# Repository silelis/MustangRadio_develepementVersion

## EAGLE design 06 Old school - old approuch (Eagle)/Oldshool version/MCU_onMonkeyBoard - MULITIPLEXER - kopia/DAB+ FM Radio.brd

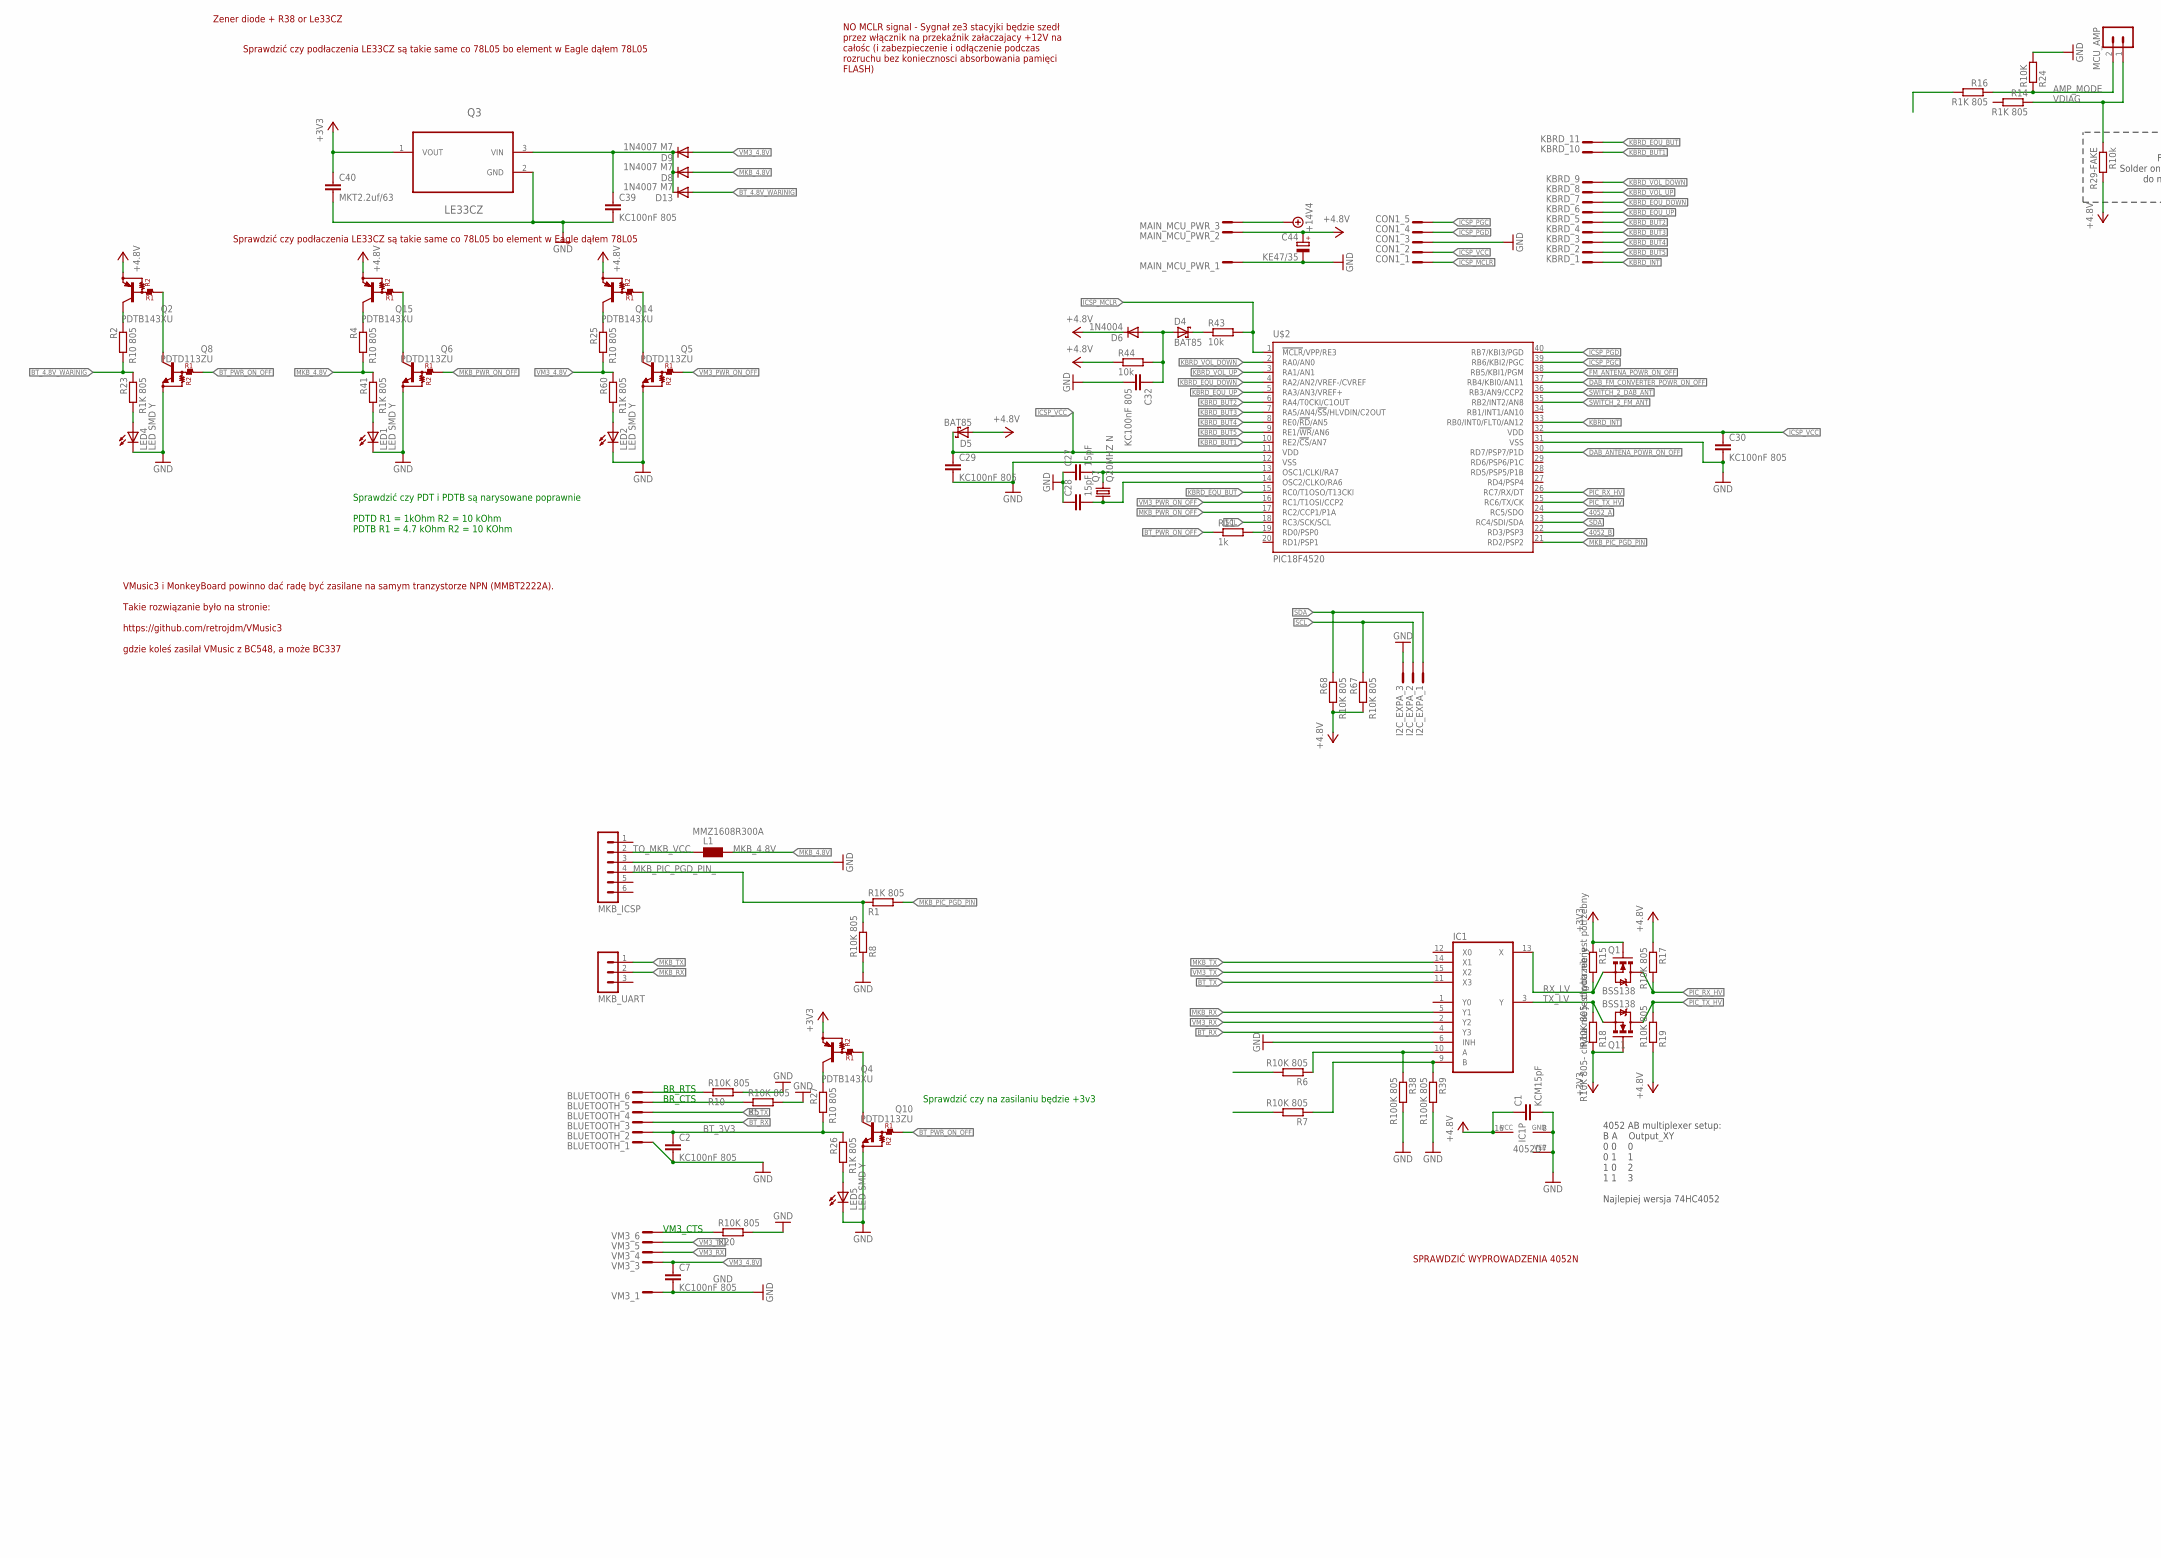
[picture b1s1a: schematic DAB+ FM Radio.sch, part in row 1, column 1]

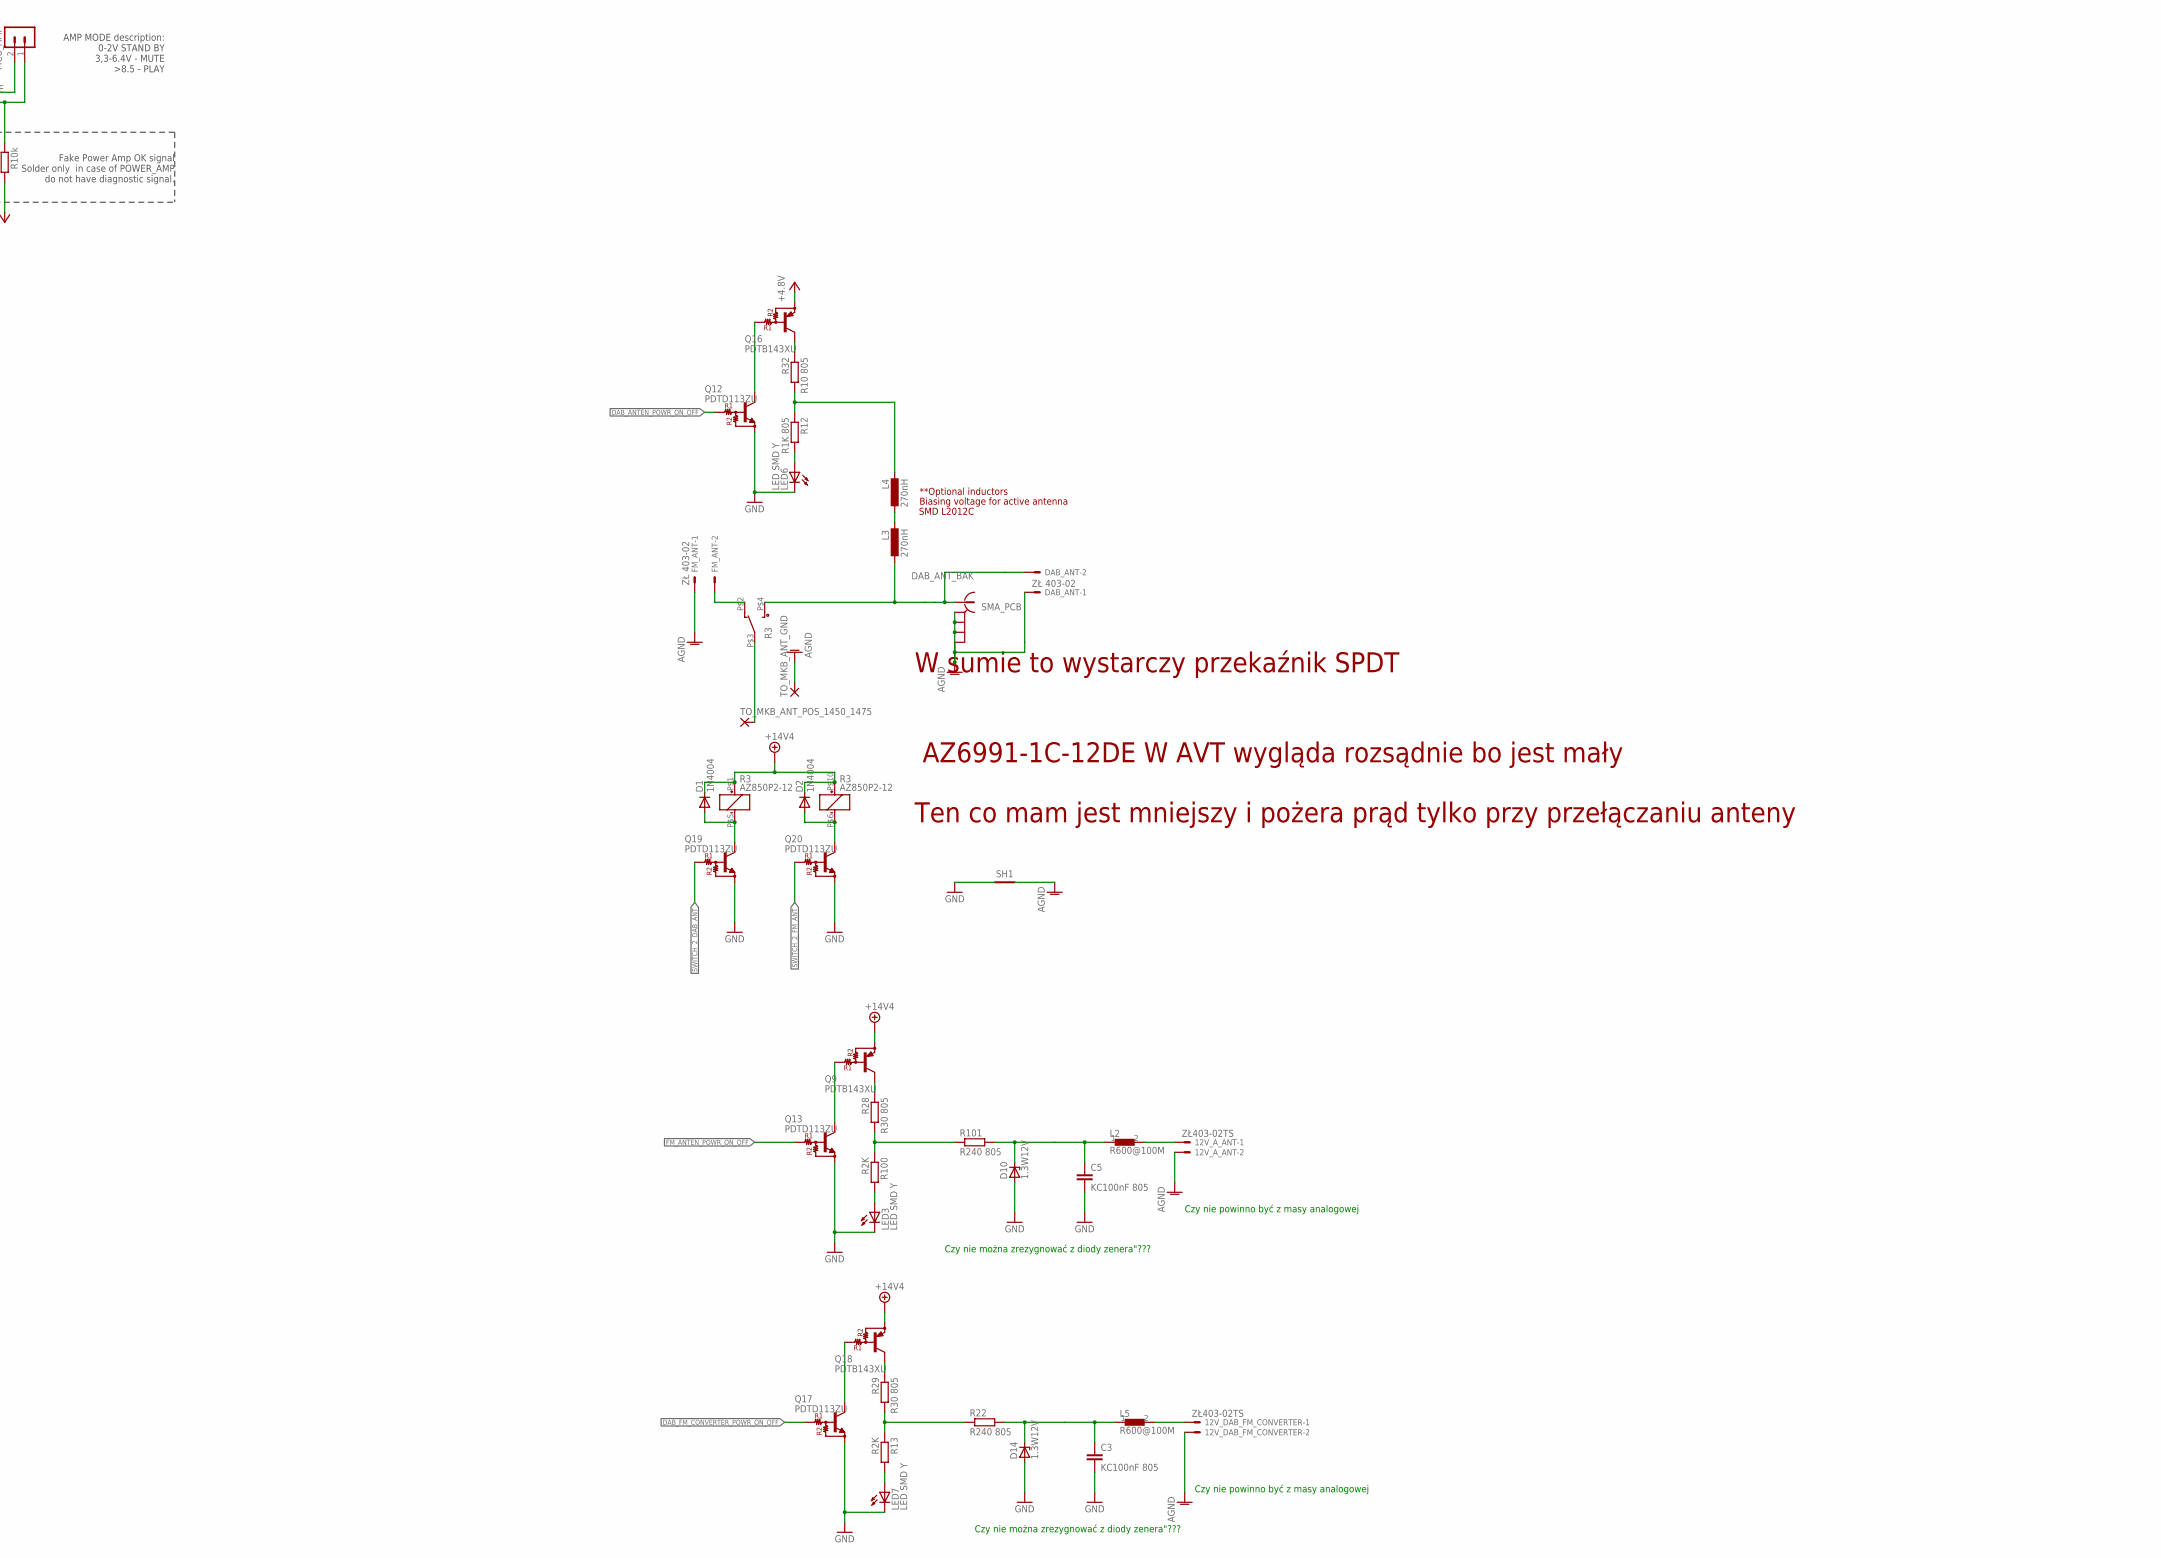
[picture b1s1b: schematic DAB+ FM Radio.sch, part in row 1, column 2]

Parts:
12V_A_ANT, 12V_DAB_FM_CONVERTER: ZŁ403-02TS; 22-23-2021
BLUETOOTH: JST_6_PIN_B6B-PH-KS; B6B-PH-KS
C1: KCM15pF; C0805
C2, C3, C5, C7, C29, C30, C32, C39: KC100nF 805; C0805
C27, C28: 15pF; C0805
C40: MKT2.2uf/63; C025-030X050
C44: KE47/35; TT2D6
CON1: JST_5_PIN_B5B-PH-KS; B5B-PH-KS
D1, D2: 1N4004; DO41-7.6
D4: BAT85; DO34-V
D5: BAT85; DO34-5
D6: 1N4004; DO41-V
D8, D9, D13: 1N4007 M7; DO41-V
D10, D14: 1.3W12V; ZDIO-2.5
DAB_ANT: ZŁ 403-02; 6410-02
DAB_ANT_BAK: SMA_PCB
FM_ANT: ZŁ 403-02; 6410-02
I2C_EXPA: JST_3_PIN_B3B-PH-KS; B3B-PH-KS
IC1: 4052D; SO16
KBRD: JST_11_PIN_B11B-PH-KS; B11B-PH-KS
L1: MMZ1608R300A; 0603
L2, L5: R600@100M; R0805
L3, L4: 270nH; L2012C
LED1, LED2, LED4, LED5: LED SMD Y; CHIP-LED0805
LED3, LED6, LED7: LED SMD Y; SMARTLED-TTW
MAIN_MCU_PWR: JST_3_PIN_B3B-XH-A; B3B-XH-A
MCU_AMP: MA02-1
MKB_ICSP: MA06-1
MKB_UART: MA03-1
Q1, Q11: BSS138; SOT23-3
Q2, Q4, Q9, Q14, Q15, Q16, Q18: PDTB143XU; SOT-23
Q3: LE33CZ; TO127P254X749-3
Q5, Q6, Q8, Q10, Q12, Q13, Q17, Q19, Q20: PDTD113ZU; SOT-23
Q7: Q20MHZ N; HC49/S
R1, R12, R14, R16, R23, R26, R41, R60: R1K 805; R0805
R2, R4, R25, R27, R32: R10 805; R0805
R3: AZ850P2-12; AZ850-2C
R5, R6, R7, R8, R10, R17, R19, R20, R67, R68: R10K 805; R0805
R11: 1k; R0805
R13, R100: R2K; R0805
R15, R18: R10K 805- chyba nie jest potrzebny; R0805
R22, R101: R240 805; M0805
R24: R10K; R0805
R28, R29: R30 805; R0805
R29-FAKE: R10k; 0204/7
R38, R39: R100K 805; M0805
R43: 10k; R0805
R44: 10k; M0805
SH1: SHORT-HT5; SHORT_TOP-50
TO_MKB_ANT_GND: 2,54/0,8
TO_MKB_ANT_POS_1450_1475: 2,54/0,8
U$2: PIC18F4520; DIL40
VM3: JST_6_PIN_B6B-PH-KS; B6B-PH-KS

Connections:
4052_A: R6.2, U$2.24 (RC5/SDO)
4052_B: R7.2, U$2.22 (RD3/PSP3)
+3V3: C40.1, Q1.1 (G), Q3.1 (VOUT), Q4.2 (E), Q11.1 (G), R15.1, R18.1
+5V: C1.1, C44.+, D5.A, D6.C, IC1.16 (VCC), MAIN_MCU_PWR.P$2, Q2.2 (E), Q14.2 (E), Q15.2 (E), Q16.2 (E), R17.1, R19.1, R29-FAKE.2, R44.1, R67.2, R68.2
+14V4: D1.C, D2.C, MAIN_MCU_PWR.P$3, Q9.2 (E), Q18.2 (E), R3.P$1 (+), R3.P$10 (+)
AGND: 12V_A_ANT.2, 12V_DAB_FM_CONVERTER.2, DAB_ANT.1, DAB_ANT_BAK.GND@1 (GND), DAB_ANT_BAK.GND@2 (GND), DAB_ANT_BAK.GND@3 (GND), DAB_ANT_BAK.GND@4 (GND), FM_ANT.1, SH1.2, TO_MKB_ANT_GND.1
AMP_MODE: MCU_AMP.2, R16.1, R24.1
BT_3V3: BLUETOOTH.P$2, C2.1, R26.1, R27.2
BT_4.8V_WARINIG: D13.A, R2.2, R23.1
BT_PWR_ON_OFF: Q8.1 (B), Q10.1 (B), R11.1
BT_RX: BLUETOOTH.P$3, IC1.4 (Y3)
BT_TX: BLUETOOTH.P$4, IC1.11 (X3)
DAB_ANTENA_POWR_ON_OFF: U$2.30 (RD7/PSP7/P1D)
DAB_ANTEN_POWR_ON_OFF: Q12.1 (B)
DAB_FM_CONVERTER_POWR_ON_OFF: Q17.1 (B), U$2.37 (RB4/KBI0/AN11)
FM_ANTENA_POWR_ON_OFF: U$2.38 (RB5/KBI1/PGM)
FM_ANTEN_POWR_ON_OFF: Q13.1 (B)
GND: BLUETOOTH.P$1, C1.2, C2.2, C3.2, C5.2, C7.2, C27.1, C28.1, C29.2, C30.2, C32.2, C39.2, C40.2, C44.-, CON1.P$3, D10.A, D14.A, I2C_EXPA.P$3, IC1.6 (INH), IC1.7 (VEE), IC1.8 (GND), LED1.C, LED2.C, LED3.C@1 (C), LED4.C, LED5.C, LED6.C@1 (C), LED7.C@1 (C), MAIN_MCU_PWR.P$1, MKB_ICSP.3, Q3.2 (GND), Q5.2 (E), Q6.2 (E), Q8.2 (E), Q10.2 (E), Q12.2 (E), Q13.2 (E), Q17.2 (E), Q19.2 (E), Q20.2 (E), R5.2, R8.1, R10.2, R20.2, R24.2, R38.2, R39.2, SH1.1, U$2.12 (VSS), U$2.31 (VSS), VM3.P$1
ICSP_MCLR: CON1.P$1, R43.2, U$2.1 (!MCLR!/VPP/RE3)
ICSP_PGC: CON1.P$5, U$2.39 (RB6/KBI2/PGC)
ICSP_PGD: CON1.P$4, U$2.40 (RB7/KBI3/PGD)
ICSP_VCC: C29.1, C30.1, CON1.P$2, D5.C, U$2.11 (VDD), U$2.32 (VDD)
KBRD_BUT1: KBRD.P$10, U$2.10 (RE2/!CS!/AN7)
KBRD_BUT2: KBRD.P$5, U$2.6 (RA4/T0CKI/C1OUT)
KBRD_BUT3: KBRD.P$4, U$2.7 (RA5/AN4/!SS!/HLVDIN/C2OUT)
KBRD_BUT4: KBRD.P$3, U$2.8 (RE0/!RD!/AN5)
KBRD_BUT5: KBRD.P$2, U$2.9 (RE1/!WR!/AN6)
KBRD_EQU_BUT: KBRD.P$11, U$2.15 (RC0/T1OSO/T13CKI)
KBRD_EQU_DOWN: KBRD.P$7, U$2.4 (RA2/AN2/VREF-/CVREF)
KBRD_EQU_UP: KBRD.P$6, U$2.5 (RA3/AN3/VREF+)
KBRD_INT: KBRD.P$1, U$2.33 (RB0/INT0/FLT0/AN12)
KBRD_VOL_DOWN: KBRD.P$9, U$2.2 (RA0/AN0)
KBRD_VOL_UP: KBRD.P$8, U$2.3 (RA1/AN1)
MKB_4.8V: D8.A, L1.2, R4.2, R41.1
MKB_PIC_PGD_PIN: R1.2, U$2.21 (RD2/PSP2)
MKB_PIC_PGD_PIN_: MKB_ICSP.4, R1.1, R8.2
MKB_PWR_ON_OFF: Q6.1 (B), U$2.17 (RC2/CCP1/P1A)
MKB_RX: IC1.5 (Y1), MKB_UART.2
MKB_TX: IC1.14 (X1), MKB_UART.1
unnamed: L4.1, R12.1, R32.2
unnamed: D1.A, Q19.3 (C), R3.P$5 (-)
unnamed: R3.P$3 (5), TO_MKB_ANT_POS_1450_1475.1
unnamed: DAB_ANT.2, DAB_ANT_BAK.P$1 (1), L3.2, R3.P$4 (6)
unnamed: FM_ANT.2, R3.P$2 (4)
unnamed: D2.A, Q20.3 (C), R3.P$6 (-)
unnamed: Q2.3 (C), R2.1
unnamed: L3.1, L4.2
unnamed: IC1.9 (B), R7.1, R39.1
unnamed: C27.2, Q7.2, U$2.13 (OSC1/CLKI/RA7)
unnamed: C28.2, Q7.1, U$2.14 (OSC2/CLKO/RA6)
unnamed: R11.2, U$2.19 (RD0/PSP0)
unnamed: Q15.3 (C), R4.1
unnamed: Q2.1 (B), Q8.3 (C)
unnamed: Q12.3 (C), Q16.1 (B)
unnamed: LED4.A, R23.2
unnamed: Q4.1 (B), Q10.3 (C)
unnamed: LED6.A@1 (A), R12.2
unnamed: LED5.A, R26.2
unnamed: Q17.3 (C), Q18.1 (B)
unnamed: R13.1, R22.1, R29.2
unnamed: LED7.A@1 (A), R13.2
unnamed: Q5.3 (C), Q14.1 (B)
unnamed: C3.1, D14.C, L5.1, R22.2
unnamed: 12V_DAB_FM_CONVERTER.1, L5.2
unnamed: LED2.A, R60.2
unnamed: Q14.3 (C), R25.1
unnamed: Q16.3 (C), R32.1
unnamed: Q9.3 (C), R28.1
unnamed: Q18.3 (C), R29.1
unnamed: Q4.3 (C), R27.1
unnamed: Q6.3 (C), Q15.1 (B)
unnamed: BLUETOOTH.P$5, R5.1
unnamed: LED1.A, R41.2
unnamed: D4.C, R43.1
unnamed: C32.1, D4.A, D6.A, R44.2
unnamed: BLUETOOTH.P$6, R10.1
unnamed: R20.1, VM3.P$6
unnamed: IC1.10 (A), R6.1, R38.1
unnamed: C39.1, D8.C, D9.C, D13.C, Q3.3 (VIN)
unnamed: Q9.1 (B), Q13.3 (C)
unnamed: R28.2, R100.1, R101.1
unnamed: LED3.A@1 (A), R100.2
unnamed: C5.1, D10.C, L2.1, R101.2
unnamed: 12V_A_ANT.1, L2.2
PIC_RX_HV: Q1.3 (D), R17.2, U$2.26 (RC7/RX/DT)
PIC_TX_HV: Q11.3 (D), R19.2, U$2.25 (RC6/TX/CK)
RX_LV: IC1.13 (X), Q1.2 (S), R15.2
SCL: I2C_EXPA.P$2, R67.1, U$2.18 (RC3/SCK/SCL)
SDA: I2C_EXPA.P$1, R68.1, U$2.23 (RC4/SDI/SDA)
SWITCH_2_DAB_ANT: Q19.1 (B), U$2.36 (RB3/AN9/CCP2)
SWITCH_2_FM_ANT: Q20.1 (B), U$2.35 (RB2/INT2/AN8)
TO_MKB_VCC: L1.1, MKB_ICSP.2
TX_LV: IC1.3 (Y), Q11.2 (S), R18.2
VDIAG: MCU_AMP.1, R14.1, R29-FAKE.1
VM3_4.8V: C7.1, D9.A, R25.2, R60.1, VM3.P$3
VM3_PWR_ON_OFF: Q5.1 (B), U$2.16 (RC1/T1OSI/CCP2)
VM3_RX: IC1.2 (Y2), VM3.P$4
VM3_TX: IC1.15 (X2), VM3.P$5

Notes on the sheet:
AMP MODE description: 0-2V STAND BY 3,3-6.4V - MUTE >8.5 - PLAY
Fake Power Amp OK signal Solder only in case of POWER_AMP do not have diagnostic signal.
NO MCLR signal - Sygnał ze3 stacyjki będzie szedł przez włącznik na przekaźnik załaczajacy +12V na całośc (i zabezpieczenie i odłączenie podczas rozruchu bez koniecznosci absorbowania pamięci FLASH)
Sprawdzić czy podłaczenia LE33CZ są takie same co 78L05 bo element w Eagle dąłem 78L05
Sprawdzić czy PDT i PDTB są narysowane poprawnie PDTD R1 = 1kOhm R2 = 10 kOhm PDTB R1 = 4.7 kOhm R2 = 10 KOhm
W sumie to wystarczy przekaźnik SPDT AZ6991-1C-12DE W AVT wygląda rozsądnie bo jest mały Ten co mam jest mniejszy i pożera prąd tylko przy przełączaniu anteny
**Optional inductors
Biasing voltage for active antenna
SMD L2012C
Czy nie powinno być z masy analogowej
VMusic3 i MonkeyBoard powinno dać radę być zasilane na samym tranzystorze NPN (MMBT2222A). Takie rozwiązanie było na stronie: https://github.com/retrojdm/VMusic3 gdzie koleś zasilał VMusic z BC548, a może BC337
SPRAWDZIĆ WYPROWADZENIA 4052N
4052 AB multiplexer setup: B A Output_XY 0 0 0 0 1 1 1 0 2 1 1 3 Najlepiej wersja 74HC4052
VM3_CTS
BR_CTS
BR_RTS
Sprawdzić czy na zasilaniu będzie +3v3
Czy nie można zrezygnować z diody zenera"???
Zener diode + R38 or Le33CZ

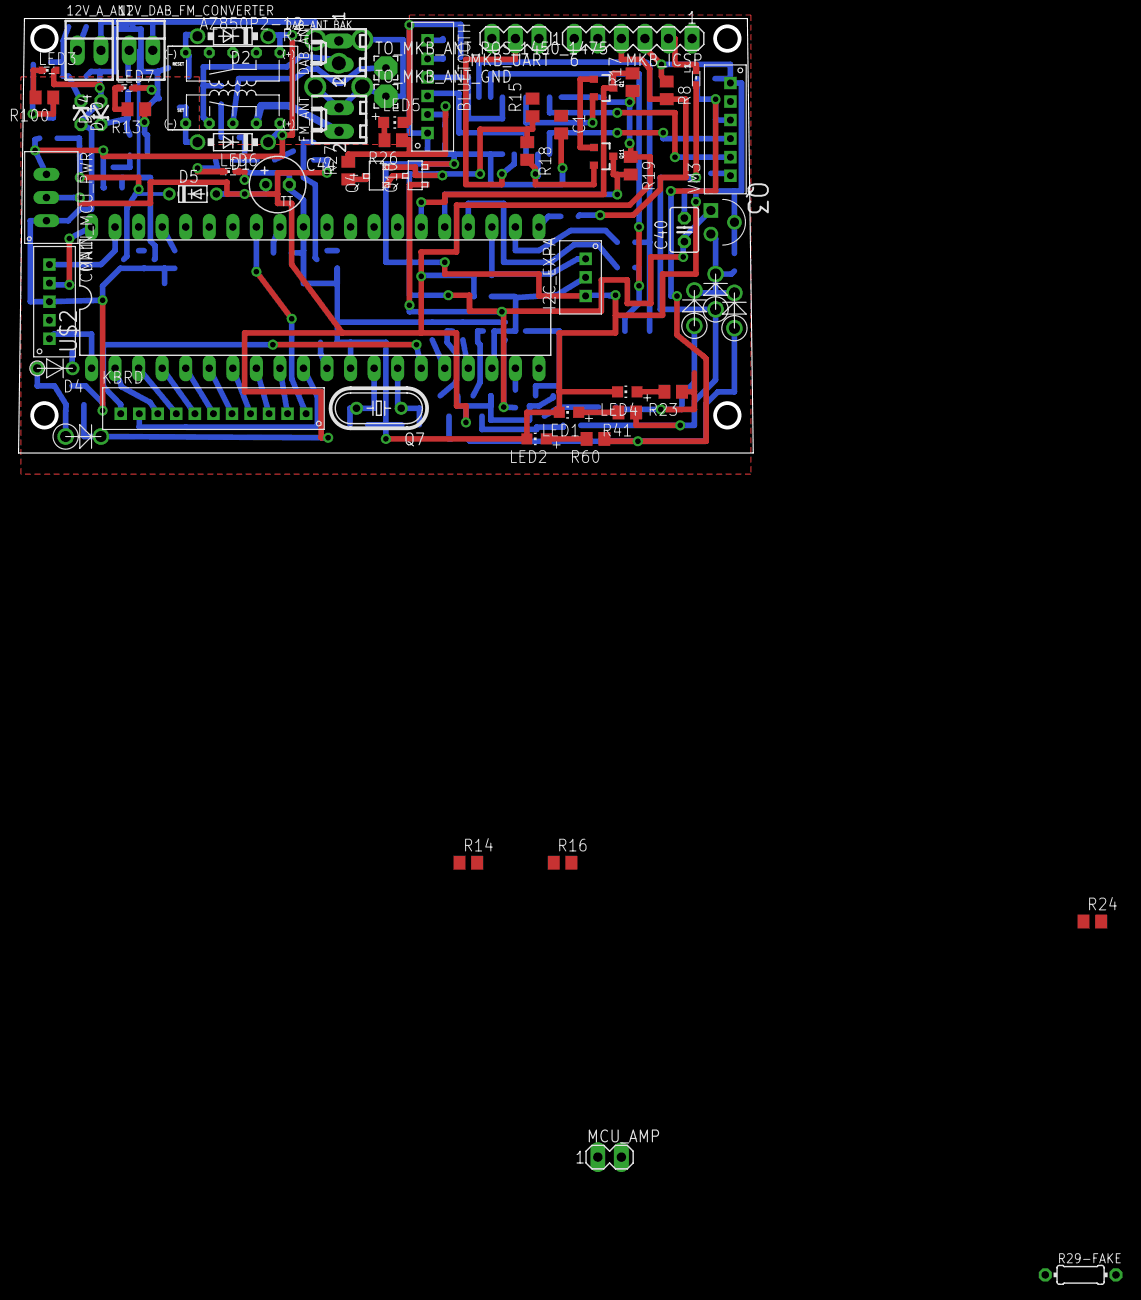
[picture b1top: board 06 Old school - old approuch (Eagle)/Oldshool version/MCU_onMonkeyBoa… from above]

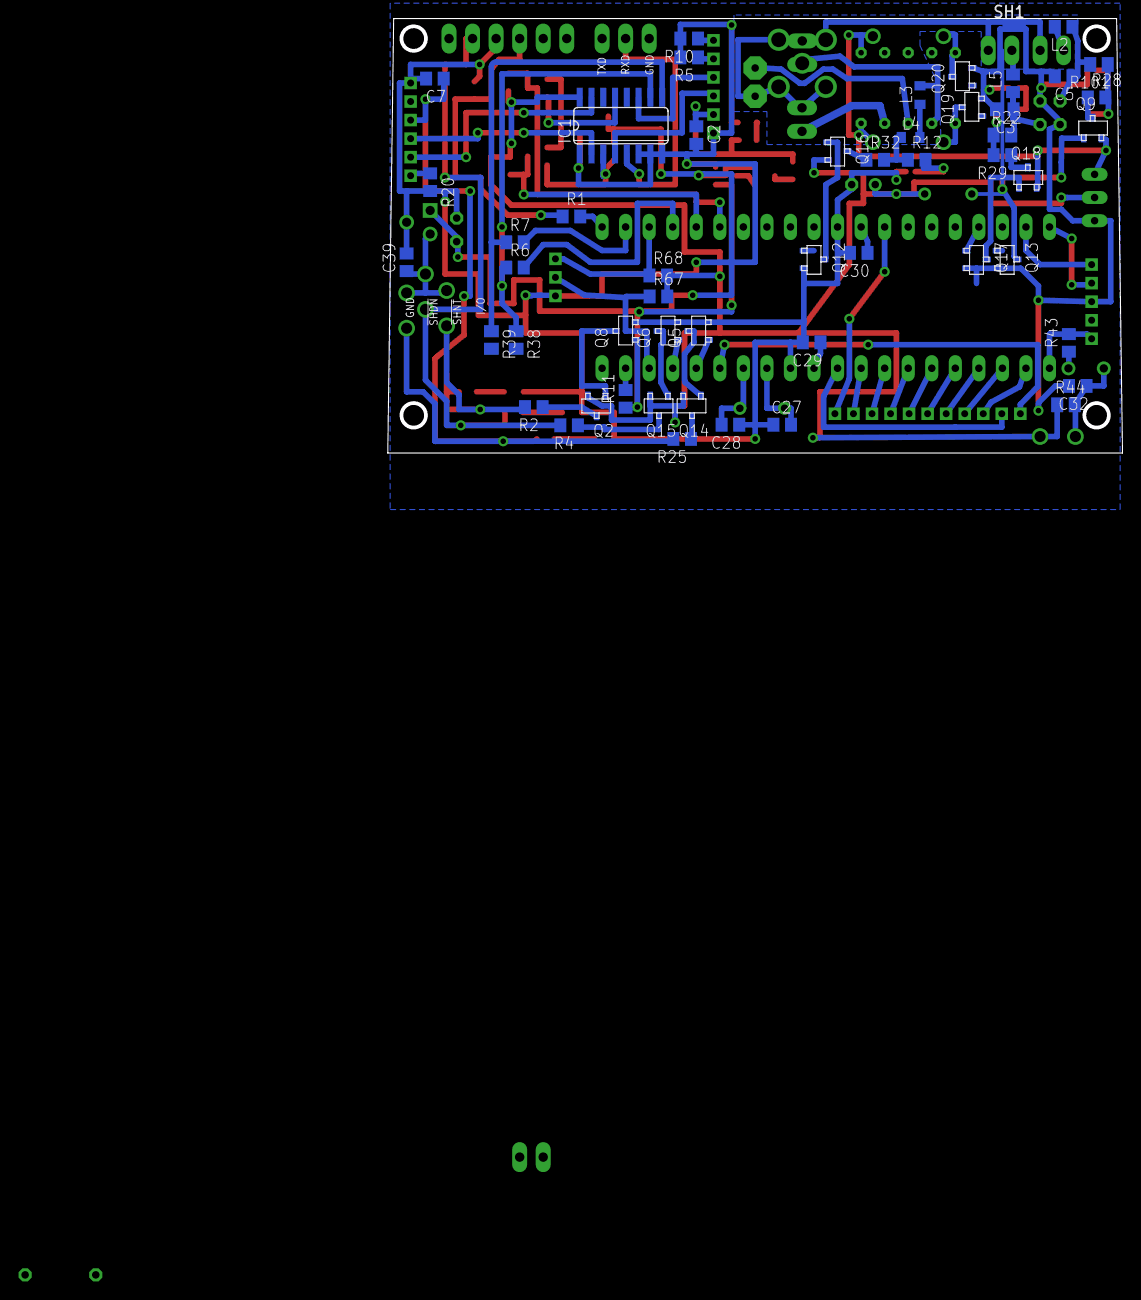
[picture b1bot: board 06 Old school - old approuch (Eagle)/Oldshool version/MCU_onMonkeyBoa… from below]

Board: 2 copper layers, 79.2 x 46.9 mm, 113 parts (52 on the bottom side), 94 nets.

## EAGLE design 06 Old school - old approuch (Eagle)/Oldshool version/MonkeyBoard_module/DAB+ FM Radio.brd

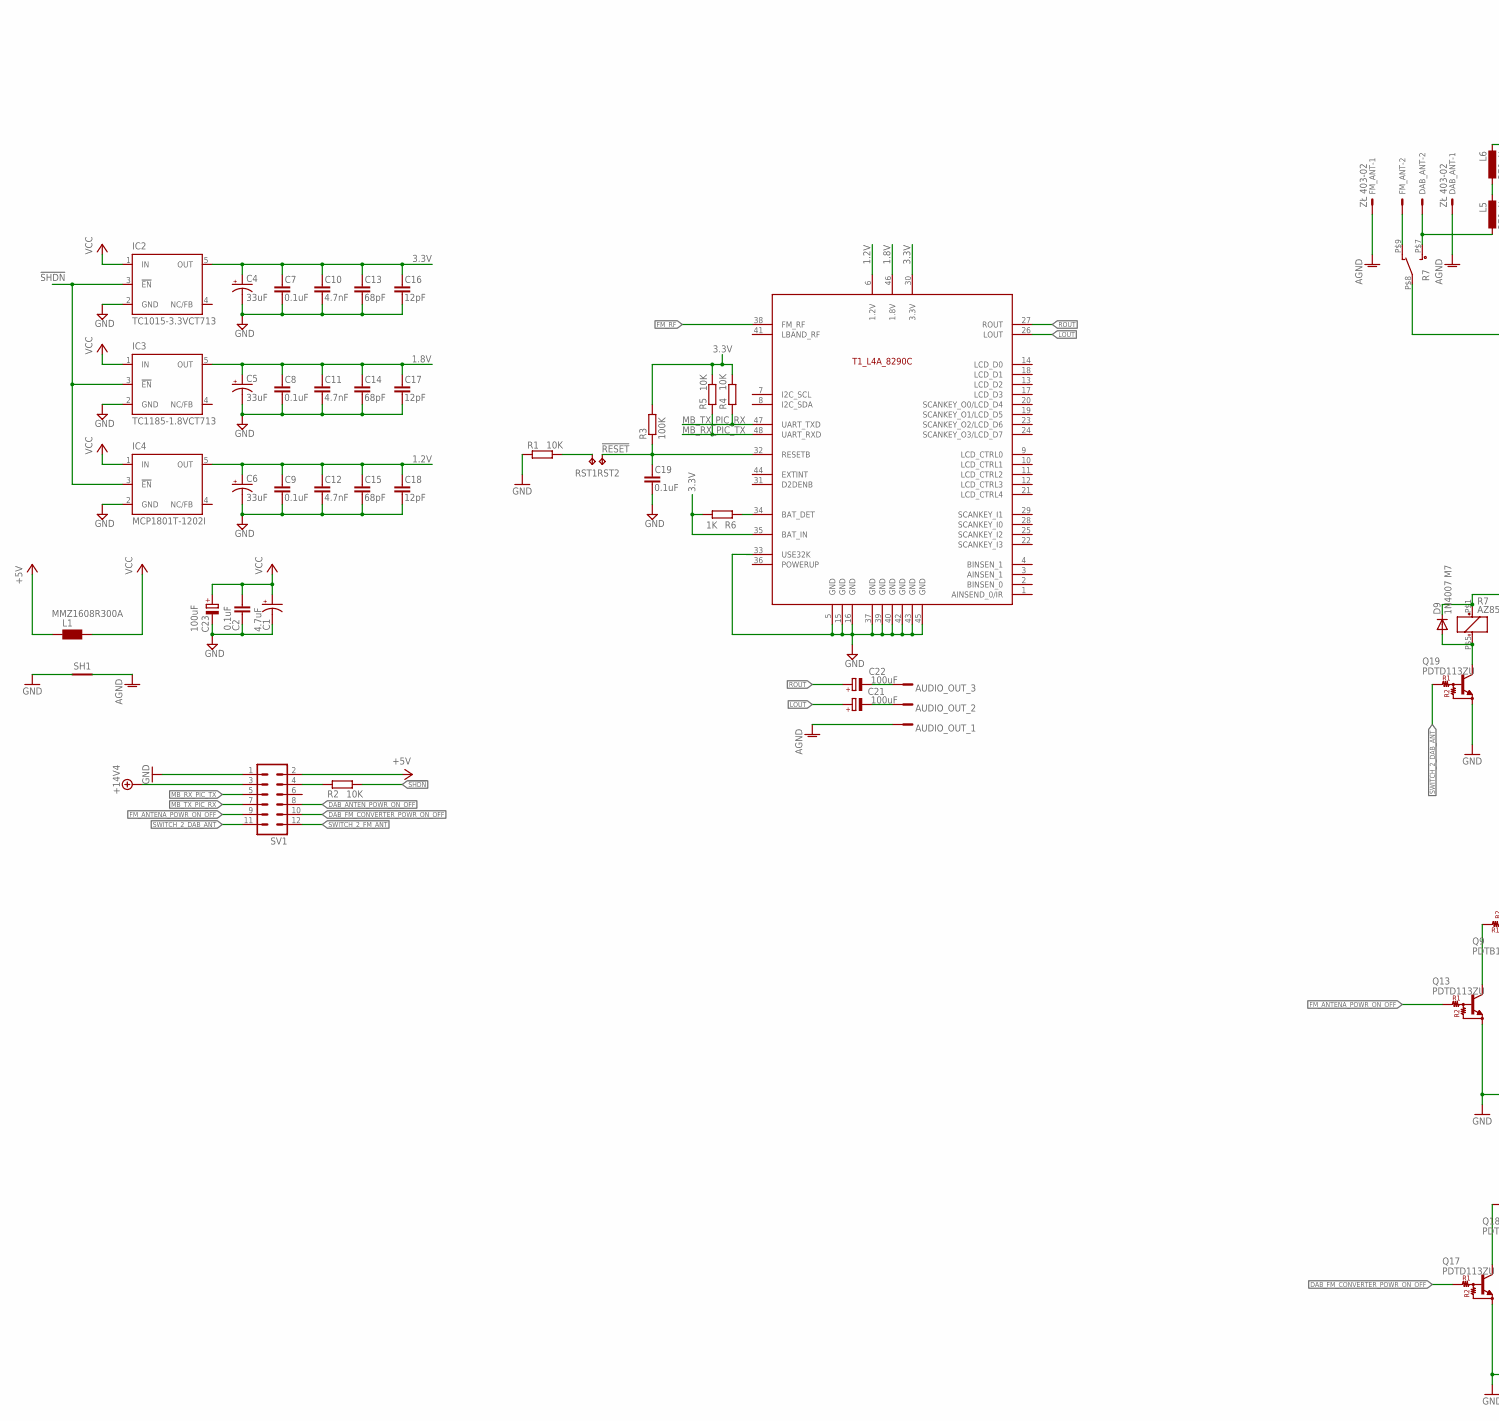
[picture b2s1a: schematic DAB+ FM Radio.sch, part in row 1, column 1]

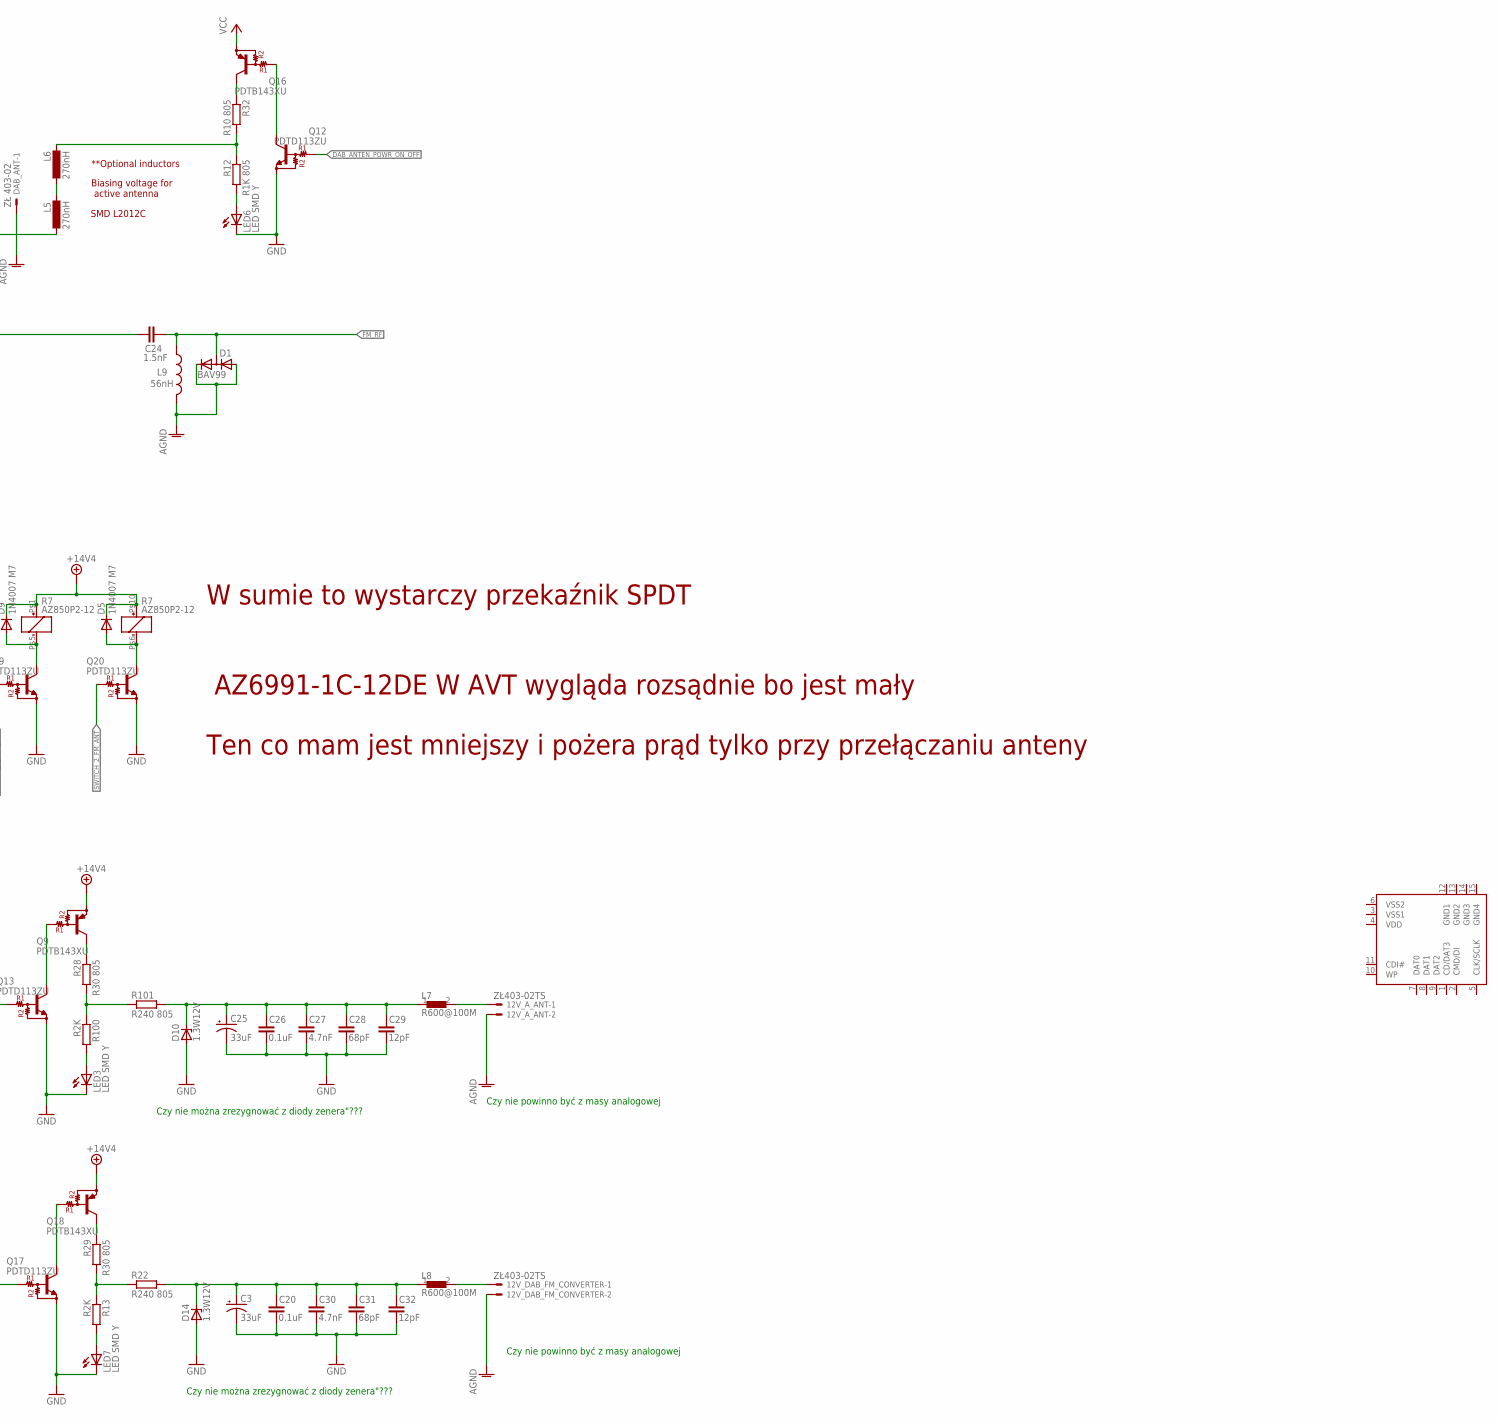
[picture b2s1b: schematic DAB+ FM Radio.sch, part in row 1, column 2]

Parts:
12V_A_ANT, 12V_DAB_FM_CONVERTER: ZŁ403-02TS; 22-23-2021
AUDIO_OUT: JST_3_PIN_B3B-PH-KS; B3B-PH-KS
C1: 4.7uF; EIA3216
C2, C7, C8, C9, C19, C20, C26: 0.1uF; C0603
C3, C4, C5, C6, C25: 33uF; EIA3216
C10, C11, C12, C27, C30: 4.7nF; C0603
C13, C14, C15, C28, C31: 68pF; C0603
C16, C17, C18, C29, C32: 12pF; C0603
C21, C22, C23: 100uF; PANASONIC_D
C24: 1.5nF; C0603
D1: BAV99; SOT23
D5, D9: 1N4007 M7; SOD-123_MINI-SMA
D10, D14: 1.3W12V; ZDIO-2.5
DAB_ANT: ZŁ 403-02; 6410-02
FM_ANT: ZŁ 403-02; 6410-02
IC2: TC1015-3.3VCT713; SOT23-DBV
IC3: TC1185-1.8VCT713; SOT23-DBV
IC4: MCP1801T-1202I; SOT23-DBV
L1: MMZ1608R300A; 0603
L5, L6: 270nH; L2012C
L7, L8: R600@100M; R0805
L9: 56nH; 0603
LED3, LED6, LED7: LED SMD Y; SMARTLED-TTW
Q9, Q16, Q18: PDTB143XU; SOT-23
Q12, Q13, Q17, Q19, Q20: PDTD113ZU; SOT-23
R1, R2, R4, R5: 10K; R0603
R3: 100K; R0603
R6: 1K; R0603
R7: AZ850P2-12; AZ850-2C
R12: R1K 805; R0805
R13, R100: R2K; R0805
R22, R101: R240 805; M0805
R28, R29: R30 805; R0805
R32: R10 805; R0805
RST1, RST2: TPB1,27; B1,27
SH1: SHORT-HT5; SHORT_TOP-50
SV1: MA06-2
U$1: T1_L4A_8290C/T2_L4A_8650C; T1_L4A
U$6: ZŁ KART SD; SDCMF-10915W010

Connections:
1.2V: C6.A (+), C9.1, C12.1, C15.1, C18.1, IC4.5 (OUT), U$1.6 (1.2V)
1.8V: C5.A (+), C8.1, C11.1, C14.1, C17.1, IC3.5 (OUT), U$1.46 (1.8V)
3.3V: C4.A (+), C7.1, C10.1, C13.1, C16.1, IC2.5 (OUT), R3.2, R4.2, R5.2, R6.2, U$1.30 (3.3V), U$1.35 (BAT_IN)
!RESET!: C19.1, R3.1, RST2.TP, U$1.32 (RESETB)
!SHDN!: IC2.3 (!EN), IC3.3 (!EN), IC4.3 (!EN), R2.2
+5V: L1.1, SV1.2
+12V: D5.C, D9.C, Q9.2 (E), Q18.2 (E), R7.P$1 (+), R7.P$10 (+), SV1.3
AGND: 12V_A_ANT.2, 12V_DAB_FM_CONVERTER.2, AUDIO_OUT.P$1, D1.1 (A), D1.2 (C), DAB_ANT.1, FM_ANT.1, L9.2, SH1.2
DAB_ANTEN_POWR_ON_OFF: Q12.1 (B), SV1.8
DAB_FM_CONVERTER_POWR_ON_OFF: Q17.1 (B), SV1.10
FM_ANTENA_POWR_ON_OFF: Q13.1 (B), SV1.9
FM_RF: C24.2, D1.3 (AC), L9.1, U$1.38 (FM_RF)
GND: C1.C (-), C2.2, C3.C (-), C4.C (-), C5.C (-), C6.C (-), C7.2, C8.2, C9.2, C10.2, C11.2, C12.2, C13.2, C14.2, C15.2, C16.2, C17.2, C18.2, C19.2, C20.2, C23.-, C25.C (-), C26.2, C27.2, C28.2, C29.2, C30.2, C31.2, C32.2, D10.A, D14.A, IC2.2 (GND), IC3.2 (GND), IC4.2 (GND), LED3.C@1 (C), LED6.C@1 (C), LED7.C@1 (C), Q12.2 (E), Q13.2 (E), Q17.2 (E), Q19.2 (E), Q20.2 (E), R1.1, SH1.1, SV1.1, U$1.5 (GND), U$1.15 (GND), U$1.16 (GND), U$1.33 (USE32K), U$1.37 (GND), U$1.39 (GND), U$1.40 (GND), U$1.42 (GND), U$1.43 (GND), U$1.45 (GND)
GND1: U$6.12 (GND1)
GND2: U$6.13 (GND2)
GND3: U$6.14 (GND3)
GND4: U$6.15 (GND4)
LOUT: C21.+, U$1.26 (LOUT)
MB_RX_PIC_TX: R5.1, SV1.5, U$1.48 (UART_RXD)
MB_TX_PIC_RX: R4.1, SV1.7, U$1.47 (UART_TXD)
unnamed: D5.A, Q20.3 (C), R7.P$6 (-)
unnamed: D9.A, Q19.3 (C), R7.P$5 (-)
unnamed: R6.1, U$1.34 (BAT_DET)
unnamed: C24.1, R7.P$8 (5)
unnamed: DAB_ANT.2, L5.2, R7.P$7 (6)
unnamed: AUDIO_OUT.P$3, C22.-
unnamed: FM_ANT.2, R7.P$9 (4)
unnamed: AUDIO_OUT.P$2, C21.-
unnamed: L6.1, R12.1, R32.2
unnamed: R2.1, SV1.4
unnamed: L5.1, L6.2
unnamed: R1.2, RST1.TP
unnamed: Q12.3 (C), Q16.1 (B)
unnamed: LED6.A@1 (A), R12.2
unnamed: Q17.3 (C), Q18.1 (B)
unnamed: R13.1, R22.1, R29.2
unnamed: LED7.A@1 (A), R13.2
unnamed: C3.A (+), C20.1, C30.1, C31.1, C32.1, D14.C, L8.1, R22.2
unnamed: 12V_DAB_FM_CONVERTER.1, L8.2
unnamed: Q16.3 (C), R32.1
unnamed: Q9.3 (C), R28.1
unnamed: Q18.3 (C), R29.1
unnamed: Q9.1 (B), Q13.3 (C)
unnamed: R28.2, R100.1, R101.1
unnamed: LED3.A@1 (A), R100.2
unnamed: C25.A (+), C26.1, C27.1, C28.1, C29.1, D10.C, L7.1, R101.2
unnamed: 12V_A_ANT.1, L7.2
ROUT: C22.+, U$1.27 (ROUT)
SWITCH_2_DAB_ANT: Q19.1 (B), SV1.11
SWITCH_2_FM_ANT: Q20.1 (B), SV1.12
VCC: C1.A (+), C2.1, C23.+, IC2.1 (IN), IC3.1 (IN), IC4.1 (IN), L1.2, Q16.2 (E)
VDD: U$6.4 (VDD)
VSS1: U$6.3 (VSS1)
VSS2: U$6.6 (VSS2)

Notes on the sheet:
W sumie to wystarczy przekaźnik SPDT AZ6991-1C-12DE W AVT wygląda rozsądnie bo jest mały Ten co mam jest mniejszy i pożera prąd tylko przy przełączaniu anteny
**Optional inductors
Biasing voltage for active antenna
SMD L2012C
Czy nie powinno być z masy analogowej
Czy nie można zrezygnować z diody zenera"???

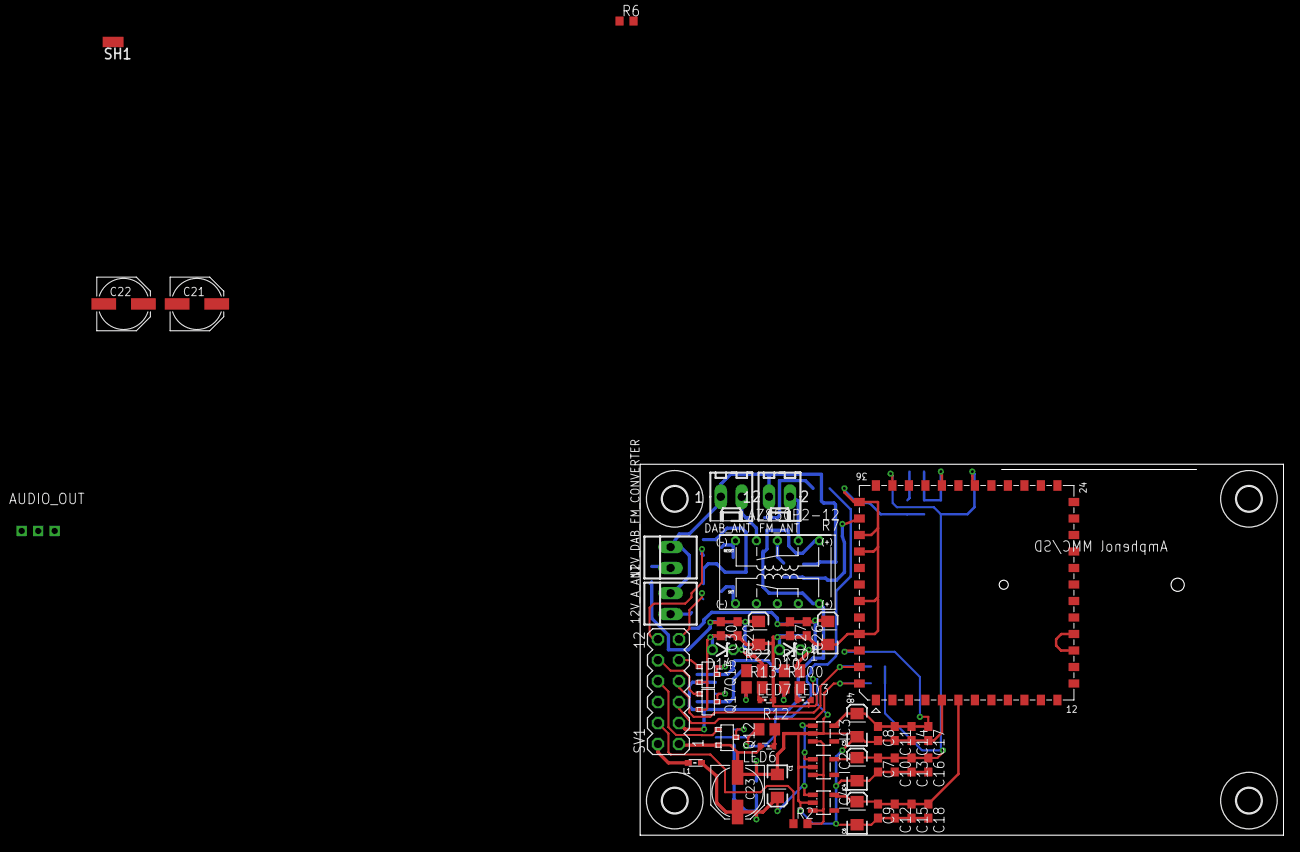
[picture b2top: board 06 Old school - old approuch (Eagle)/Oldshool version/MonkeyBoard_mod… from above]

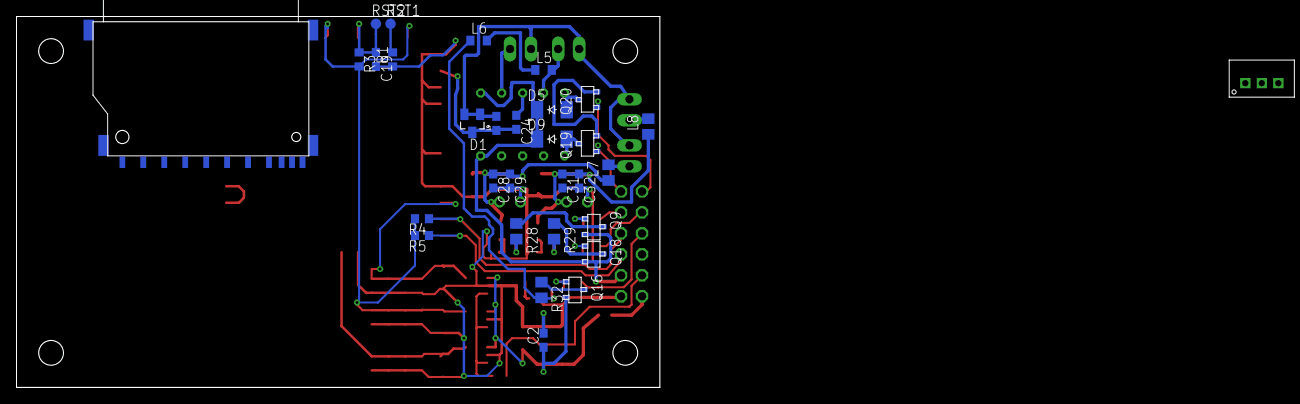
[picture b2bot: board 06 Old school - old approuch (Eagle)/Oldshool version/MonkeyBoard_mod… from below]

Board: 2 copper layers, 78.0 x 45.0 mm, 87 parts (30 on the bottom side), 47 nets.

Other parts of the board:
U$2, U$3, U$4, U$5: 3,0

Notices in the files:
parts and their libraries:
SparkFun-FreqCtrl: Licensing: Creative Commons ShareAlike 4.0 International - https://creativecommons.org/licenses/by-sa/4.0
diy-modules: Released under the Creative Commons Attribution 4.0 International License: http://creativecommons.org/licenses/by/4.0
